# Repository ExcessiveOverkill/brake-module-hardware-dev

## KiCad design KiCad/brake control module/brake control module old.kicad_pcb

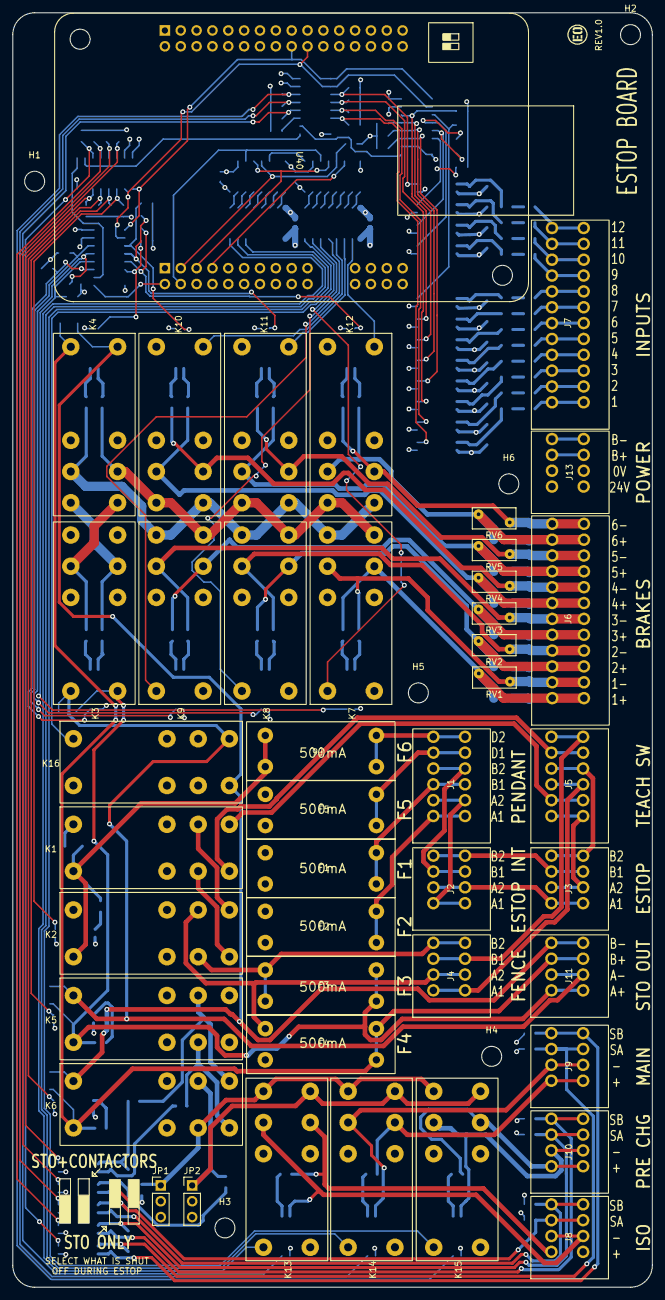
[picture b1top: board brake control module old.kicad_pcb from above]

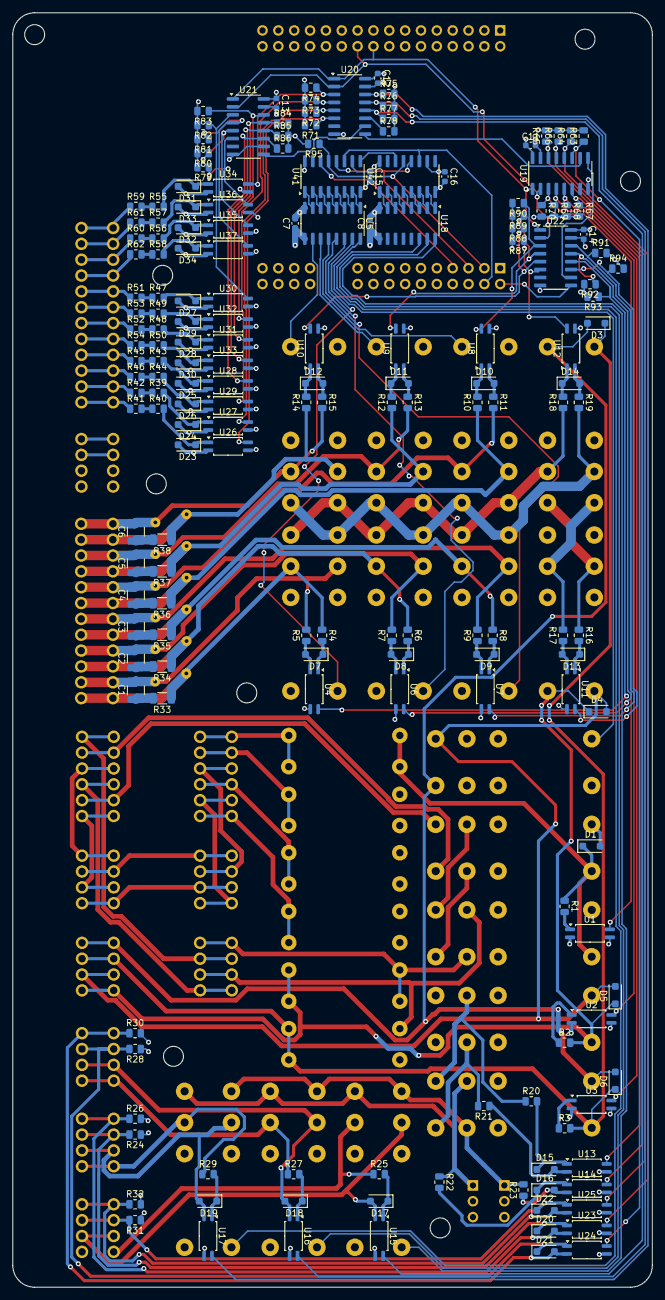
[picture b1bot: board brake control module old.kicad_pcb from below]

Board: 4 copper layers, 102.5 x 204.2 mm, 230 parts (181 on the bottom side), 197 nets.

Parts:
C1, C2, C3, C4, C5, C6: .47uf; C_1210_3225Metric
C7, C8, C11, C12, C13, C14, C15, C16: 1uf; C_0603_1608Metric
D1, D3, D4, D5, D6, D7, D8, D9, D10, D11, D12, D13, D14, D15, D16, D17, D18, D19, D20, D21, D22, D23, D24, D25, D26, D27, D28, D29, D30, D31, D32, D33, D34: D; D_SOD-123F
F1, F2, F3, F4, F5, F6: Fuse; 5x20mm fuse
H1, H2, H3, H4, H5, H6: MountingHole; MountingHole_3.2mm_M3
J1: PENDANT ESTOP + DMS; DORABO DB141V-2.54-6P-GN
J2: ESTOP CONTROLLER; DORABO DB141V-2.54-4P-GN
J3: ESTOP EXTERNAL; DORABO DB141V-2.54-4P-GN
J4: FENCE; DORABO DB141V-2.54-4P-GN
J5: TEACH SWITCH; DORABO DB141V-2.54-6P-GN
J6: BRAKES; DORABO DB141V-2.54-12P-GN
J7: INPUTS; DORABO DB141V-2.54-12P-GN
J8: ISO_CONTACTOR; DORABO DB141V-2.54-4P-GN
J9: MAIN_CONTACTOR; DORABO DB141V-2.54-4P-GN
J10: PRECHARGE_CONTACTOR; DORABO DB141V-2.54-4P-GN
J11: STO OUT; DORABO DB141V-2.54-4P-GN
J13: POWER; DORABO DB141V-2.54-4P-GN
JP1, JP2: Jumper_2_Open; PinHeader_1x03_P2.54mm_Vertical
K1, K2, K3, K4, K5, K6, K7, K8, K9, K10, K11, K12, K13, K14, K15, K16: Relay_DPDT; az733 form C
R1, R2, R3, R4, R5, R6, R7, R8, R9, R10, R11, R12, R13, R14, R15, R16, R17, R18, R19, R20, R21, R22, R23, R25, R27, R29, R63, R64, R65, R66, R67, R68, R69, R70, R71, R72, R73, R74, R75, R76, R77, R78, R79, R80, R81, R82, R83, R84, R85, R86, R87, R88, R89, R90, R91, R92, R93, R94, R95: 220k; R_0805_2012Metric
R24, R26, R28, R30, R31, R32, R39, R40, R41, R42, R43, R44, R45, R46, R47, R48, R49, R50, R51, R52, R53, R54, R55, R56, R57, R58, R59, R60, R61, R62: 2.2k; R_0805_2012Metric
R33, R34, R35, R36, R37, R38: 470; R_1206_3216Metric
RV1, RV2, RV3, RV4, RV5, RV6: Varistor; RV_Disc_D7mm_W3.4mm_P5mm
U1, U2, U3, U4, U6, U7, U8, U9, U10, U11, U12, U13, U14, U15, U16, U17, U23, U24, U25, U26, U27, U28, U29, U30, U31, U32, U33, U34, U35, U36, U37: 140357145400; SOP-4_4.4x2.6mm_P1.27mm
U5, U18: ULN2003; SOIC-16_3.9x9.9mm_P1.27mm
U19, U20, U21, U22: 74HC165; SOIC-16_3.9x9.9mm_P1.27mm
U40: EM_serial_module
U41, U42: 74HC595; SOIC-16_3.9x9.9mm_P1.27mm

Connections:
0V_CHAIN_A: D4.2 (A), D5.2 (A), J11.2, K3.8, K5.8, K16.5
0V_CHAIN_B: D3.2 (A), D6.2 (A), J11.4, K4.8, K6.8, K16.4
+3.3V: C11.1, C12.1, C13.1, C14.1, C15.1, C16.1, R63.2, R64.2, R65.2, R66.2, R67.2, R68.2, R69.2, R70.2, R71.2, R72.2, R73.2, R74.2, R75.2, R76.2, R77.2, R78.2, R79.2, R80.2, R81.2, R82.2, R83.2, R84.2, R85.2, R86.2, R87.2, R88.2, R89.2, R90.2, R91.2, R92.2, R93.2, R94.2, R95.2, U19.16 (VCC), U20.16 (VCC), U21.16 (VCC), U22.16 (VCC), U40.A29 (3.3V), U41.10 (~SRCLR), U41.16 (VCC), U42.10 (~SRCLR), U42.16 (VCC)
+24V: C7.1, C8.1, K7.1, K8.1, K9.1, K10.1, K11.1, K12.1, K13.1, K14.1, K15.1, K16.1, U5.9 (COM), U18.9 (COM), U40.B32 (24V_ISO)
+24V_2: F1.1, F2.1, F5.1, J13.1, JP2.2 (B), K5.5, R24.1, R28.1, R31.1
+24V_CHAIN_A: D4.1 (K), D5.1 (K), F3.2, J11.1, K3.1, K5.1, R2.2
+24V_CHAIN_B: D3.1 (K), D6.1 (K), F4.2, J11.3, K4.1, K6.1, R3.2
BRAKE_1_RETURN: C1.2, J6.2, K7.6, R5.2, RV1.2
BRAKE_1_SUPPLY: J6.1, K7.3, R4.1, R33.1, RV1.1
BRAKE_2_RETURN: C2.2, J6.4, K8.6, R7.2, RV2.2
BRAKE_2_SUPPLY: J6.3, K8.3, R6.1, R34.1, RV2.1
BRAKE_3_RETURN: C3.2, J6.6, K9.6, R9.2, RV3.2
BRAKE_3_SUPPLY: J6.5, K9.3, R8.1, R35.1, RV3.1
BRAKE_4_RETURN: C4.2, J6.8, K10.6, R11.2, RV4.2
BRAKE_4_SUPPLY: J6.7, K10.3, R10.1, R36.1, RV4.1
BRAKE_5_RETURN: C5.2, J6.10, K11.6, R13.2, RV5.2
BRAKE_5_SUPPLY: J6.9, K11.3, R12.1, R37.1, RV5.1
BRAKE_6_RETURN: C6.2, J6.12, K12.6, R15.2, RV6.2
BRAKE_6_SUPPLY: J6.11, K12.3, R14.1, R38.1, RV6.1
BRK_1_FBK: R93.1, U4.4, U22.12 (D1)
BRK_2_FBK: R92.1, U6.4, U22.13 (D2)
BRK_3_FBK: R91.1, U7.4, U22.14 (D3)
BRK_4_FBK: R90.1, U8.4, U22.3 (D4)
BRK_5_FBK: R89.1, U9.4, U22.4 (D5)
BRK_6_FBK: R88.1, U10.4, U22.5 (D6)
BRK_A_FBK: R94.1, U11.4, U22.11 (D0)
BRK_B_FBK: R87.1, U12.4, U22.6 (D7)
BRK_RELAY_1: K7.8, U5.15 (O2)
BRK_RELAY_2: K8.8, U5.14 (O3)
BRK_RELAY_3: K9.8, U5.13 (O4)
BRK_RELAY_4: K10.8, U5.12 (O5)
BRK_RELAY_5: K11.8, U5.11 (O6)
BRK_RELAY_6: K12.8, U5.10 (O7)
CHAIN_A_FBK: R69.1, U2.4, U19.4 (D5)
CHAIN_A_RELAY_FBK: R67.1, U13.4, U19.6 (D7)
CHAIN_B_FBK: R68.1, U3.4, U19.5 (D6)
CHAIN_B_RELAY_FBK: R65.1, U14.4, U19.14 (D3)
CHAIN_RELAY: K16.8, U5.16 (O1)
DMS_FBK: R70.1, U1.4, U19.3 (D4)
EXT_BRAKE_RETURN: J13.4, K3.4
EXT_BRAKE_SUPPLY: J13.3, K3.5
GND: C7.2, C8.2, C11.2, C12.2, C13.2, C14.2, C15.2, C16.2, U1.3, U2.3, U3.3, U4.3, U5.8 (GND), U6.3, U7.3, U8.3, U9.3, U10.3, U11.3, U12.3, U13.3, U14.3, U15.3, U16.3, U17.3, U18.8 (GND), U19.8 (GND), U19.15 (~CE), U20.8 (GND), U20.15 (~CE), U21.8 (GND), U21.10 (DS), U21.15 (~CE), U22.8 (GND), U22.15 (~CE), U23.3, U24.3, U25.3, U26.3, U27.3, U28.3, U29.3, U30.3, U31.3, U32.3, U33.3, U34.3, U35.3, U36.3, U37.3, U40.A1 (GND), U40.A9 (GND), U40.A17 (GND), U40.A23 (GND), U40.A25 (GND), U40.A31 (GND), U40.B1 (GND), U40.B9 (GND), U40.B17 (GND), U40.B31 (GND_ISO), U41.8 (GND), U42.8 (GND)
GND2: D1.2 (A), D23.2 (A), D24.2 (A), D25.2 (A), D26.2 (A), D27.2 (A), D28.2 (A), D29.2 (A), D30.2 (A), D31.2 (A), D32.2 (A), D33.2 (A), D34.2 (A), J13.2, JP1.2 (B), K1.8, K2.8, K5.4, K16.3, K16.6, R26.2, R30.2, R32.2, U1.2, U2.2, U3.2, U26.2, U27.2, U28.2, U29.2, U30.2, U31.2, U32.2, U33.2, U34.2, U35.2, U36.2, U37.2
INPUT_1: R71.1, U20.6 (D7), U26.4
INPUT_2: R72.1, U20.5 (D6), U27.4
INPUT_3: R73.1, U20.4 (D5), U29.4
INPUT_4: R86.1, U21.11 (D0), U28.4
INPUT_5: R85.1, U21.12 (D1), U33.4
INPUT_6: R84.1, U21.13 (D2), U31.4
INPUT_7: R83.1, U21.14 (D3), U32.4
INPUT_8: R82.1, U21.3 (D4), U30.4
INPUT_9: R81.1, U21.4 (D5), U37.4
INPUT_10: R80.1, U21.5 (D6), U35.4
INPUT_11: R79.1, U21.6 (D7), U36.4
INPUT_12: R74.1, U20.3 (D4), U34.4
INPUT_CLK: U19.2 (CP), U20.2 (CP), U21.2 (CP), U22.2 (CP), U40.A20 (PB7)
INPUT_DATA: U22.9 (Q7), U40.B2 (PB0)
INPUT_LOAD: U19.1 (~PL), U20.1 (~PL), U21.1 (~PL), U22.1 (~PL), U40.A18 (PB9)
INT_BRAKE_RETURN: K4.3, K7.5, K8.5, K9.5, K10.5, K11.5, K12.5, R19.2
INT_BRAKE_SUPPLY: K4.6, K7.4, K8.4, K9.4, K10.4, K11.4, K12.4, R18.1
ISO_CONTACTOR_RETURN: D17.2 (A), J8.2, K13.6, U15.2
ISO_CONTACTOR_SUPPLY: J8.1, K13.3, R25.1
ISO_CON_FBK: R77.1, U15.4, U20.12 (D1)
ISO_CON_FBK_EXT: R66.1, U19.13 (D2), U25.4
ISO_CON_FBK_EXT_A: D22.1 (K), J8.3, R31.2, U25.1
ISO_CON_FBK_EXT_B: D22.2 (A), J8.4, R32.1, U25.2
ISO_CON_RELAY: K13.8, U18.16 (O1)
MAIN_CONTACTOR_RETURN: D18.2 (A), J9.2, K14.6, U16.2
MAIN_CONTACTOR_SUPPLY: J9.1, K14.3, R27.1
MAIN_CON_FBK: R76.1, U16.4, U20.13 (D2)
MAIN_CON_FBK_EXT: R63.1, U19.11 (D0), U24.4
MAIN_CON_FBK_EXT_A: D21.1 (K), J9.3, R28.2, U24.1
MAIN_CON_FBK_EXT_B: D21.2 (A), J9.4, R30.1, U24.2
MAIN_CON_RELAY: K14.8, U18.15 (O2)
unnamed: C1.1, R33.2
unnamed: C2.1, R34.2
unnamed: C3.1, R35.2
unnamed: C4.1, R36.2
unnamed: C5.1, R37.2
unnamed: C6.1, R38.2
unnamed: D1.1 (K), F6.2, K1.1, K2.1, R1.1
unnamed: D7.2 (A), R5.1, U4.2
unnamed: D7.1 (K), R4.2, U4.1
unnamed: D8.2 (A), R7.1, U6.2
unnamed: D8.1 (K), R6.2, U6.1
unnamed: D9.2 (A), R9.1, U7.2
unnamed: D9.1 (K), R8.2, U7.1
unnamed: D10.2 (A), R11.1, U8.2
unnamed: D10.1 (K), R10.2, U8.1
unnamed: D11.2 (A), R13.1, U9.2
unnamed: D11.1 (K), R12.2, U9.1
unnamed: D12.2 (A), R15.1, U10.2
unnamed: D12.1 (K), R14.2, U10.1
unnamed: D13.2 (A), R17.1, U11.2
unnamed: D13.1 (K), R16.2, U11.1
unnamed: D14.2 (A), R19.1, U12.2
unnamed: D14.1 (K), R18.2, U12.1
unnamed: D15.2 (A), R21.1, U13.2
unnamed: D15.1 (K), R20.2, U13.1
unnamed: D16.2 (A), R23.1, U14.2
unnamed: D16.1 (K), R22.2, U14.1
unnamed: D17.1 (K), R25.2, U15.1
unnamed: D18.1 (K), R27.2, U16.1
unnamed: D19.1 (K), R29.2, U17.1
unnamed: D23.1 (K), R40.2, U26.1
unnamed: D24.1 (K), R39.2, U27.1
unnamed: D25.1 (K), R43.2, U28.1
unnamed: D26.1 (K), R44.2, U29.1
unnamed: D27.1 (K), R47.2, U30.1
unnamed: D28.1 (K), R48.2, U31.1
unnamed: D29.1 (K), R49.2, U32.1
unnamed: D30.1 (K), R50.2, U33.1
unnamed: D31.1 (K), R55.2, U34.1
unnamed: D32.1 (K), R56.2, U35.1
unnamed: D33.1 (K), R57.2, U36.1
unnamed: D34.1 (K), R58.2, U37.1
unnamed: F2.2, J1.1
unnamed: J1.2, J2.1
unnamed: F1.2, J1.3
unnamed: J1.4, J2.3
unnamed: F5.2, J1.5
unnamed: F6.1, J1.6
unnamed: J2.2, J3.1
unnamed: J2.4, J3.3
unnamed: J3.2, J5.1
unnamed: J3.4, J5.4
unnamed: J4.1, J5.3
unnamed: F4.1, J4.2, K2.6
unnamed: J4.3, J5.6
unnamed: F3.1, J4.4, K2.3
unnamed: J5.2, K1.5
unnamed: J5.5, K1.4
unnamed: J7.1, R41.1
unnamed: J7.2, R42.1
unnamed: J7.3, R46.1
unnamed: J7.4, R45.1
unnamed: J7.5, R54.1
unnamed: J7.6, R52.1
unnamed: J7.7, R53.1
unnamed: J7.8, R51.1
unnamed: J7.9, R62.1
unnamed: J7.10, R60.1
unnamed: J7.11, R61.1
unnamed: J7.12, R59.1
unnamed: JP1.1 (A), K6.3, K13.5, K14.5, K15.5, R23.2
unnamed: JP2.1 (A), K6.6, K13.4, K14.4, K15.4, R22.1
unnamed: K1.3, K2.4
unnamed: K1.6, K2.5
unnamed: K3.3, K4.4, R17.2
unnamed: K3.6, K4.5, R16.1
unnamed: K5.3, K6.4, R21.2
unnamed: K5.6, K6.5, R20.1
unnamed: R1.2, U1.1
unnamed: R2.1, U2.1
unnamed: R3.1, U3.1
unnamed: R39.1, R42.2
unnamed: R40.1, R41.2
unnamed: R43.1, R45.2
unnamed: R44.1, R46.2
unnamed: R47.1, R51.2
unnamed: R48.1, R52.2
unnamed: R49.1, R53.2
unnamed: R50.1, R54.2
unnamed: R55.1, R59.2
unnamed: R56.1, R60.2
unnamed: R57.1, R61.2
unnamed: R58.1, R62.2
unnamed: U18.1 (I1), U42.7 (QH)
unnamed: U18.2 (I2), U42.6 (QG)
unnamed: U18.3 (I3), U42.5 (QF)
unnamed: U18.4 (I4), U42.4 (QE)
unnamed: U18.5 (I5), U42.3 (QD)
unnamed: U18.6 (I6), U42.2 (QC)
unnamed: U18.7 (I7), U42.1 (QB)
unnamed: U19.10 (DS), U20.9 (Q7)
unnamed: U19.9 (Q7), U22.10 (DS)
unnamed: R78.1, U20.11 (D0)
unnamed: U20.10 (DS), U21.9 (Q7)
unnamed: U5.7 (I7), U41.1 (QB)
unnamed: U5.6 (I6), U41.2 (QC)
unnamed: U5.5 (I5), U41.3 (QD)
unnamed: U5.4 (I4), U41.4 (QE)
unnamed: U5.3 (I3), U41.5 (QF)
unnamed: U5.2 (I2), U41.6 (QG)
unnamed: U41.9 (QH'), U42.14 (SER)
unnamed: U5.1 (I1), U41.7 (QH)
OUTPUT_CLK: U40.B4 (PB2), U41.11 (SRCLK), U42.11 (SRCLK)
OUTPUT_DATA: U40.B7 (PB13), U41.14 (SER)
OUTPUT_ENABLE: R95.1, U40.B3 (PB1), U41.13 (~OE), U42.13 (~OE)
OUTPUT_WRITE: U40.B5 (PB10), U41.12 (RCLK), U42.12 (RCLK)
PRECHARGE_CONTACTOR_RETURN: D19.2 (A), J10.2, K15.6, U17.2
PRECHARGE_CONTACTOR_SUPPLY: J10.1, K15.3, R29.1
PRE_CON_FBK: R75.1, U17.4, U20.14 (D3)
PRE_CON_FBK_EXT: R64.1, U19.12 (D1), U23.4
PRE_CON_FBK_EXT_A: D20.1 (K), J10.3, R24.2, U23.1
PRE_CON_FBK_EXT_B: D20.2 (A), J10.4, R26.1, U23.2
PRE_CON_RELAY: K15.8, U18.14 (O3)
